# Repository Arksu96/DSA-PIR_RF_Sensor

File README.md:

View this project on [CADLAB.io](https://cadlab.io/project/26397). 

# DSA-PIR_RF_Sensor

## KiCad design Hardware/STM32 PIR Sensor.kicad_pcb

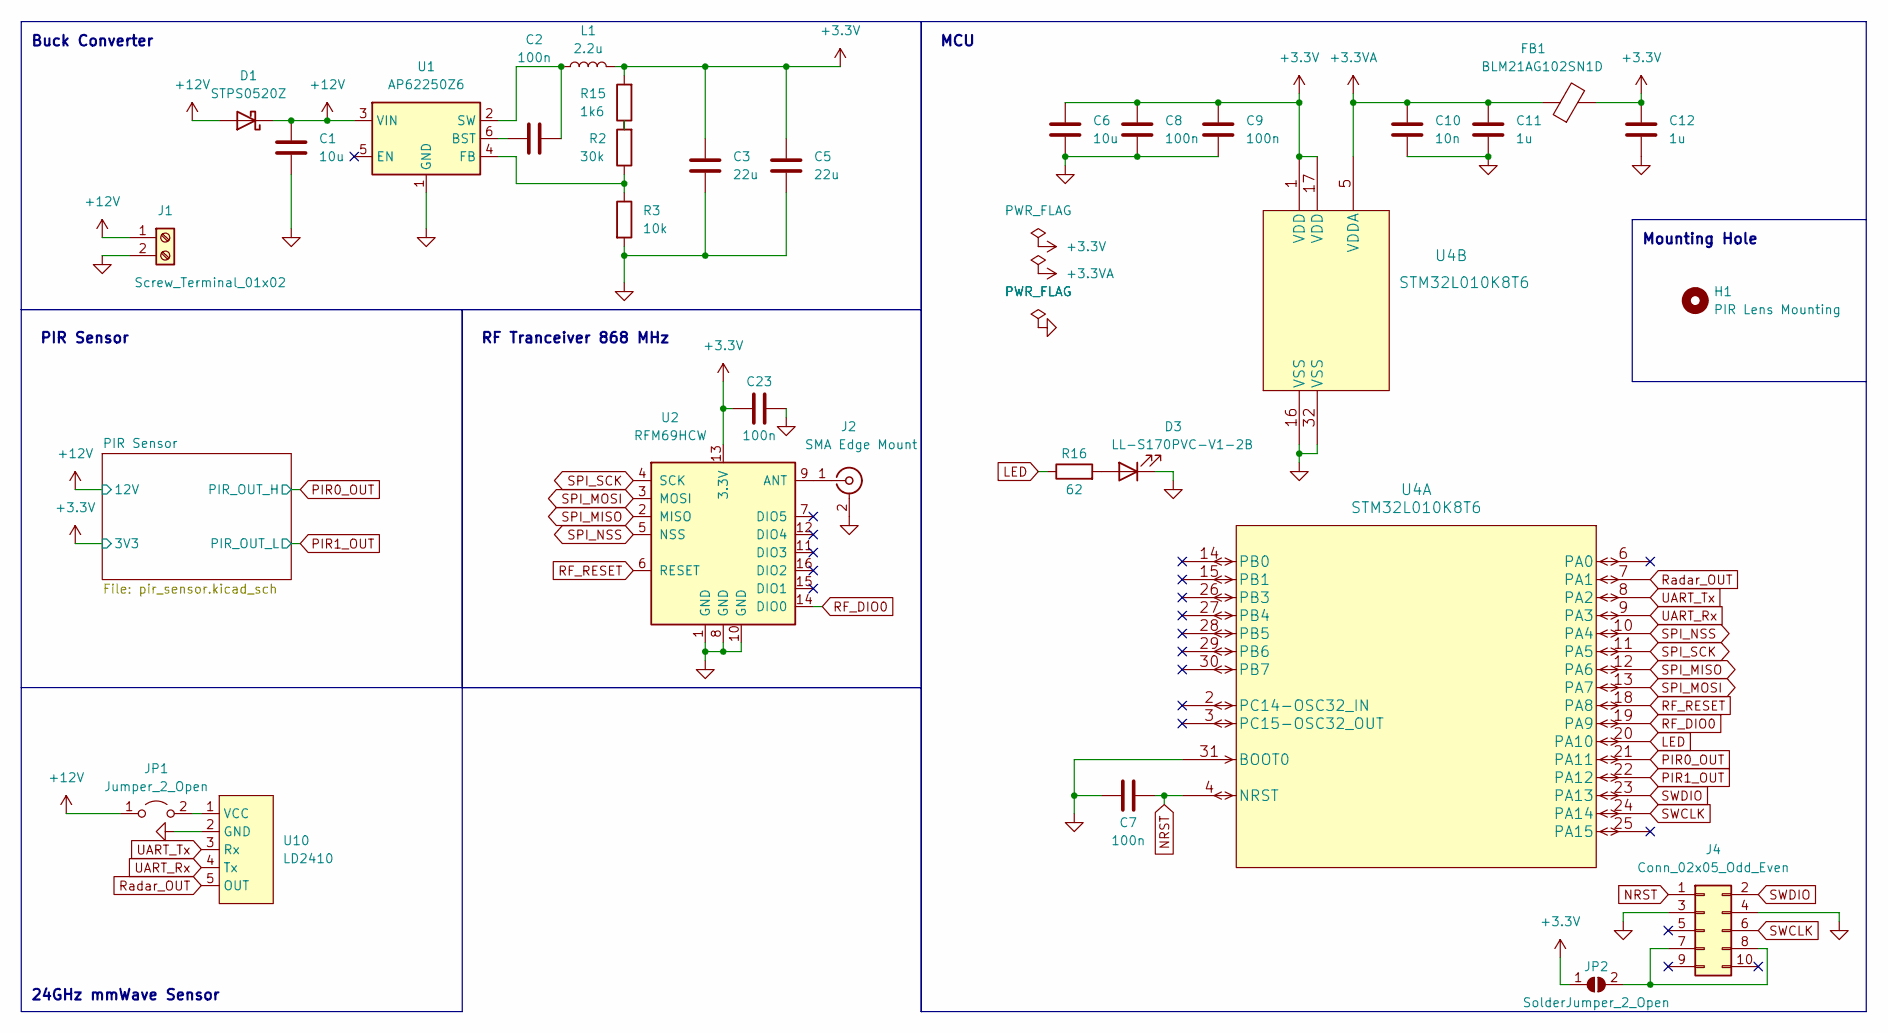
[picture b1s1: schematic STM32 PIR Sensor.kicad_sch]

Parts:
C1, C6: 10u; C_0603_1608Metric_Pad1.08x0.95mm_HandSolder
C2, C7, C8, C9, C23: 100n; C_0603_1608Metric_Pad1.08x0.95mm_HandSolder
C3, C5: 22u; C_0805_2012Metric_Pad1.18x1.45mm_HandSolder
C10: 10n; C_0603_1608Metric_Pad1.08x0.95mm_HandSolder
C11, C12: 1u; C_0603_1608Metric_Pad1.08x0.95mm_HandSolder
D1: STPS0520Z; D_SOD-123
D3: LL-S170PVC-V1-2B; LED_0805_2012Metric_Pad1.15x1.40mm_HandSolder
FB1: BLM21AG102SN1D; L_0805_2012Metric_Pad1.05x1.20mm_HandSolder
H1: PIR Lens Mounting; PIR_Mounting
J1: Screw_Terminal_01x02; DG301R-5.0
J2: SMA Edge Mount; SMA_Amphenol_132289_EdgeMount
J4: Conn_02x05_Odd_Even; IDC-Header_2x05_P2.54mm_Vertical
JP1: Jumper_2_Open; SolderJumper-2_P1.3mm_Open_TrianglePad1.0x1.5mm
JP2: SolderJumper_2_Open
L1: 2.2u; L_0805_2012Metric_Pad1.05x1.20mm_HandSolder
R2: 30k; R_0603_1608Metric_Pad0.98x0.95mm_HandSolder
R3: 10k; R_0603_1608Metric_Pad0.98x0.95mm_HandSolder
R15: 1k6; R_0603_1608Metric_Pad0.98x0.95mm_HandSolder
R16: 62; R_0603_1608Metric_Pad0.98x0.95mm_HandSolder
U1: AP62250Z6; TSOT-23-6
U2: RFM69HCW; RFM69HCW-XXXS2
U4: STM32L010K8T6; LQFP-32_7x7mm_P0.8mm
U10: LD2410

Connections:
+3.3V: C3.1, C5.1, C6.1, C8.1, C9.1, C12.1, C23.1, FB1.2, JP2.1 (A), L1.2, R15.2, U2.13 (3.3V), U4.1 (VDD), U4.17 (VDD); also elsewhere on the board
+3.3VA: C10.1, C11.1, FB1.1, U4.5 (VDDA)
+12V: C1.1, D1.1 (K), D1.2 (A), J1.1, JP1.1 (A), U1.3 (VIN); also elsewhere on the board
GND: C1.2, C3.2, C5.2, C6.2, C7.1, C8.2, C9.2, C10.2, C11.2, C12.2, C23.2, D3.1 (K), J1.2, J2.2 (Ext), J4.3, J4.4, R3.2, U1.1 (GND), U2.1 (GND), U2.8 (GND), U2.10 (GND), U4.16 (VSS), U4.31 (BOOT0), U4.32 (VSS), U10.2 (GND); also elsewhere on the board
NRST: C7.2, J4.1, U4.4 (NRST); also elsewhere on the board
unnamed: C2.1, U1.6 (BST)
unnamed: C2.2, L1.1, U1.2 (SW)
unnamed: D3.2 (A), R16.2
unnamed: J2.1 (In), U2.9 (ANT)
unnamed: J4.7, J4.8, JP2.2 (B)
unnamed: JP1.2 (B), U10.1 (VCC)
unnamed: R2.1, R3.1, U1.4 (FB)
unnamed: R2.2, R15.1
unnamed: R16.1, U4.20 (PA10)
PIR0_OUT: U4.21 (PA11); also elsewhere on the board
PIR1_OUT: U4.22 (PA12); also elsewhere on the board
RF_DIO0: U2.14 (DIO0), U4.19 (PA9)
RF_RESET: U2.6 (RESET), U4.18 (PA8)
Radar_OUT: U4.7 (PA1), U10.5 (OUT)
SCL: U4.29 (PB6); also elsewhere on the board
SDA: U4.30 (PB7); also elsewhere on the board
SPI_MISO: U2.2 (MISO), U4.12 (PA6)
SPI_MOSI: U2.3 (MOSI), U4.13 (PA7)
SPI_NSS: U2.5 (NSS), U4.10 (PA4)
SPI_SCK: U2.4 (SCK), U4.11 (PA5)
SWCLK: J4.6, U4.24 (PA14); also elsewhere on the board
SWDIO: J4.2, U4.23 (PA13); also elsewhere on the board
UART_Rx: U4.9 (PA3), U10.4 (Tx)
UART_Tx: U4.8 (PA2), U10.3 (Rx)

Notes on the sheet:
Mounting Hole
PIR Sensor
MCU
Buck Converter
24GHz mmWave Sensor
RF Tranceiver 868 MHz

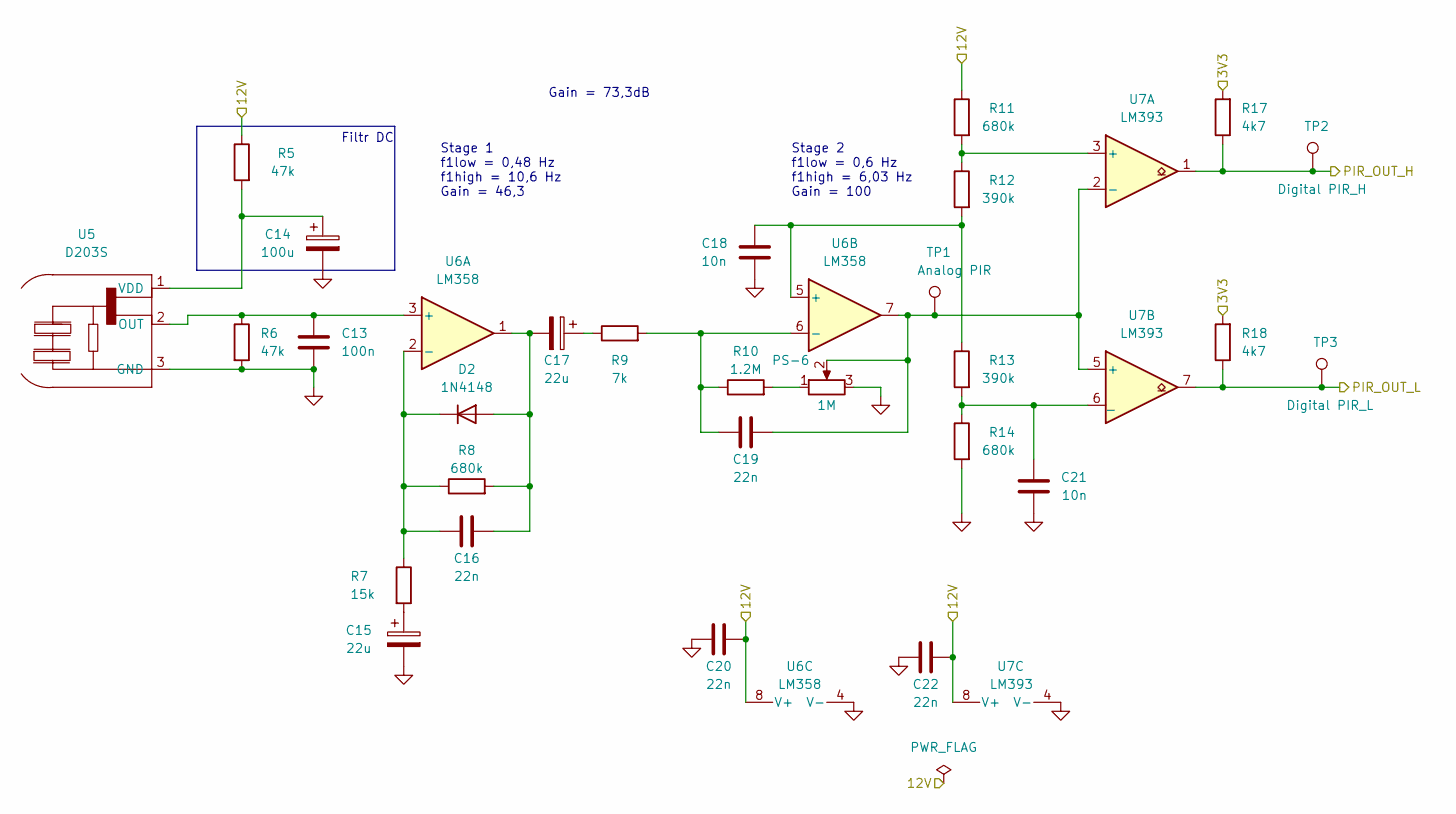
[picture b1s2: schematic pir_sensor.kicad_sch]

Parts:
C13: 100n; C_0603_1608Metric_Pad1.08x0.95mm_HandSolder
C14: 100u; CP_Elec_6.3x5.4
C15, C17: 22u; C_0805_2012Metric_Pad1.18x1.45mm_HandSolder
C16, C19, C20, C22: 22n; C_0603_1608Metric_Pad1.08x0.95mm_HandSolder
C18, C21: 10n; C_0603_1608Metric_Pad1.08x0.95mm_HandSolder
D2: 1N4148; D_MiniMELF
PS-6: 1M; Potentiometer_PS-6_Vertical_Hole
R5, R6: 47k; R_0603_1608Metric_Pad0.98x0.95mm_HandSolder
R7: 15k; R_0603_1608Metric_Pad0.98x0.95mm_HandSolder
R8, R11, R14: 680k; R_0603_1608Metric_Pad0.98x0.95mm_HandSolder
R9: 7k; R_0603_1608Metric_Pad0.98x0.95mm_HandSolder
R10: 1.2M; R_0603_1608Metric_Pad0.98x0.95mm_HandSolder
R12, R13: 390k; R_0603_1608Metric_Pad0.98x0.95mm_HandSolder
R17, R18: 4k7; R_0603_1608Metric_Pad0.98x0.95mm_HandSolder
TP1: Analog PIR; TestPoint_Pad_D1.0mm
TP2: Digital PIR_H; TestPoint_Pad_D1.0mm
TP3: Digital PIR_L; TestPoint_Pad_D1.0mm
U5: D203S; TO-5-3
U6: LM358; SO-8_5.3x6.2mm_P1.27mm
U7: LM393; SO-8_5.3x6.2mm_P1.27mm

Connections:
+3.3V: R17.2, R18.2; also elsewhere on the board
+12V: C20.2, C22.2, R5.1, R11.1, U6.8 (V+), U7.8 (V+); also elsewhere on the board
GND: C13.2, C14.2, C15.2, C18.2, C20.1, C21.2, C22.1, PS-6.3, R6.2, R14.2, U5.3 (GND), U6.4 (V-), U7.4 (V-); also elsewhere on the board
unnamed: C13.1, R6.1, U5.2 (OUT), U6.3 (+)
unnamed: C14.1, R5.2, U5.1 (VDD)
unnamed: C15.1, R7.2
unnamed: C16.1, D2.1 (K), R7.1, R8.1, U6.2 (-)
unnamed: C16.2, C17.2, D2.2 (A), R8.2, U6.1
unnamed: C17.1, R9.1
unnamed: C18.1, R12.2, R13.1, U6.5 (+)
unnamed: C19.1, R9.2, R10.1, U6.6 (-)
unnamed: C21.1, R13.2, R14.1, U7.6 (_)
unnamed: R11.2, R12.1, U7.3 (+)
PIR0_OUT: R17.1, TP2.1, U7.1; also elsewhere on the board
PIR1_OUT: R18.1, TP3.1, U7.7; also elsewhere on the board

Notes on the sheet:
Gain = 73,3dB
Filtr DC
Stage 2 f1low = 0,6 Hz f1high = 6,03 Hz Gain = 100
Stage 1 f1low = 0,48 Hz f1high = 10,6 Hz Gain = 46,3

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
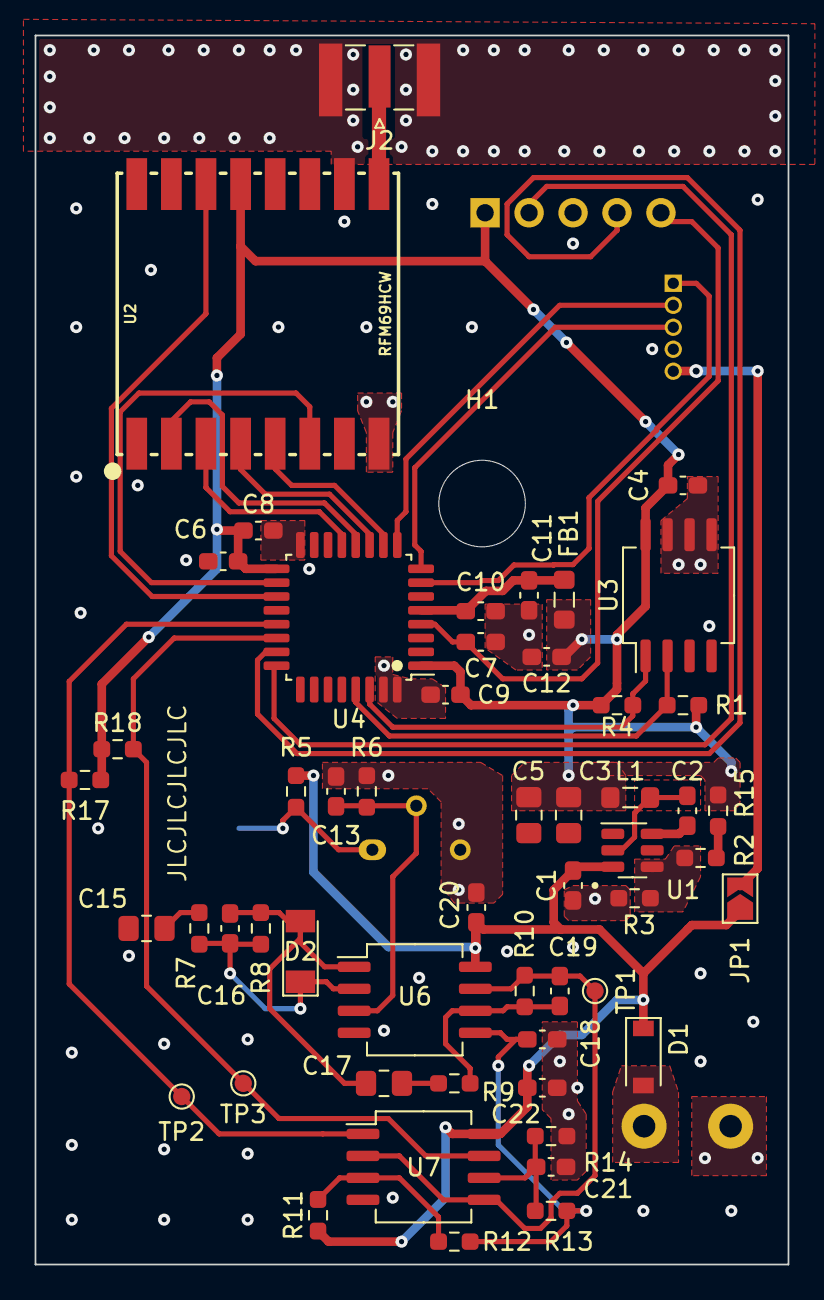
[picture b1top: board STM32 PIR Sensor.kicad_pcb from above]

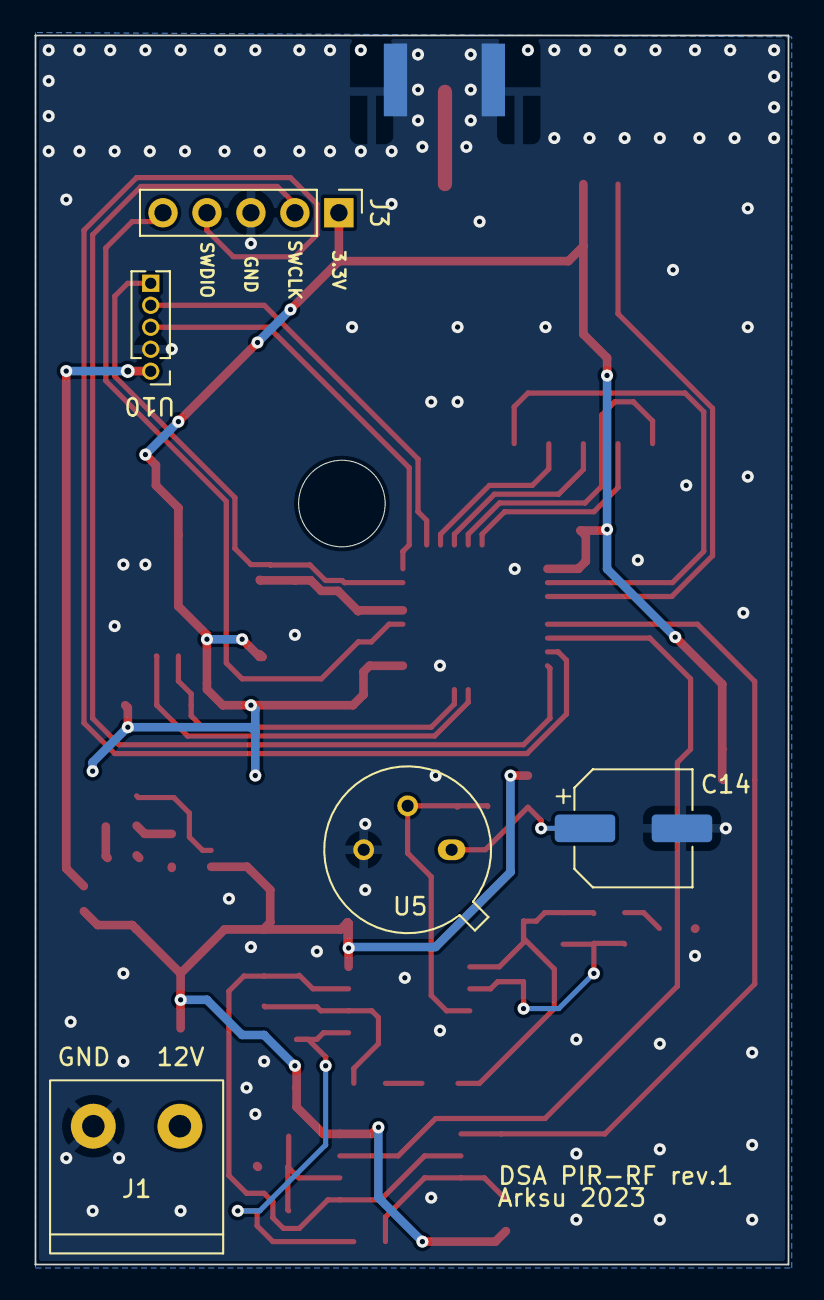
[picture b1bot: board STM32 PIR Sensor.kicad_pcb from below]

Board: 2 copper layers, 43.5 x 71.0 mm, 59 parts (5 on the bottom side), 37 nets.

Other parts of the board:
C4: 100n; C_0603_1608Metric_Pad1.08x0.95mm_HandSolder
J3: Conn_01x05_Male; PinHeader_1x05_P2.54mm_Vertical
R1, R4: 4k7; R_0603_1608Metric_Pad0.98x0.95mm_HandSolder
U3: LM75B; SO-8_5.3x6.2mm_P1.27mm

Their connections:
+3.3V: C4.2, J3.1, R1.1, R4.1, U3.8 (+Vs); also elsewhere on the board
GND: C4.1, J3.3, U3.4 (GND), U3.5 (A2), U3.6 (A1), U3.7 (A0); also elsewhere on the board
NRST: J3.5; also elsewhere on the board
SCL: R1.2, U3.2 (SCL); also elsewhere on the board
SDA: R4.2, U3.1 (SDA); also elsewhere on the board
SWCLK: J3.2; also elsewhere on the board
SWDIO: J3.4; also elsewhere on the board

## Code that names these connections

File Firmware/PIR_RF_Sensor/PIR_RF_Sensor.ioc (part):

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Mcu.Name=STM32L010K8Tx
Mcu.Package=LQFP32
Mcu.UserName=STM32L010K8Tx
PA1.GPIOParameters=GPIO_Label
PA1.GPIO_Label=Radar_OUT
PA1.Signal=GPIO_Output
PA10.GPIOParameters=GPIO_Label
PA10.GPIO_Label=LED
PA10.Signal=GPIO_Output
PA11.GPIOParameters=GPIO_Label,GPIO_ModeDefaultEXTI
PA11.GPIO_Label=PIR_H
PA11.GPIO_ModeDefaultEXTI=GPIO_MODE_IT_RISING_FALLING
PA11.Signal=GPXTI11
PA12.GPIOParameters=GPIO_Label,GPIO_ModeDefaultEXTI
PA12.GPIO_Label=PIR_L
PA12.GPIO_ModeDefaultEXTI=GPIO_MODE_IT_RISING_FALLING
PA12.Signal=GPXTI12
PA13.Mode=Serial_Wire
PA13.Signal=SYS_SWDIO
PA14.Mode=Serial_Wire
PA14.Signal=SYS_SWCLK
PA4.GPIOParameters=GPIO_Label
PA4.GPIO_Label=SPI1_NSS
PA4.Signal=GPIO_Output
PA5.Mode=Full_Duplex_Master
PA5.Signal=SPI1_SCK
PA6.Mode=Full_Duplex_Master
PA6.Signal=SPI1_MISO
PA7.Mode=Full_Duplex_Master
PA7.Signal=SPI1_MOSI
PA8.GPIOParameters=GPIO_Label
PA8.GPIO_Label=RF_Reset
PA8.Signal=GPIO_Output
PA9.GPIOParameters=GPIO_Label,GPIO_ModeDefaultEXTI
PA9.GPIO_Label=RF_Payload
PA9.GPIO_ModeDefaultEXTI=GPIO_MODE_IT_RISING
PA9.Signal=GPXTI9
RCC.SYSCLKFreq_VALUE=2097000
board=custom

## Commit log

2023-01-17 Backlink to CADLAB.io has been added.
2023-01-17 v0.1 Schematic
2023-01-22 v0.2 BOM
2023-04-01 v1.0 with issues
2023-07-06 v0.3 Init Firmware Commit
2023-08-01 v0.0.3(1) PIR&RFM69
2023-08-01 v0.0.3(2) LD2410 Init
2023-08-01 v0.0.3(3) Init corrected
2023-08-09 v0.0.4 LD2410 receiving
2023-08-14 v0.0.4(1) LD2410 crash - suspended
2023-08-14 v0.0.3(2) Stats&Msg (for review)
2023-08-16 v0.0.3(3) PIR debouce added
2023-08-16 v0.0.3(4) PIR debounce range fix
2023-08-19 v0.0.3(4) corrected PIR&RF issues
2023-09-06 v1.2.0. Prototype schematic correction
2024-05-01 RFM69 Power Level fix
2024-05-02 PIR debounce
2024-05-21 PIR RF noise debounce
2024-05-21 Gitignore update
2024-05-21 RF lib timeout
2024-05-23 Buggy Rx Tx
2024-05-25 Fixed Rx & Tx
2024-09-10 Fix: Tx interrupt Rx (freeze)
2024-10-23 Fix: IRQ disabling
2024-10-24 Fix: Working Tx&Rx
